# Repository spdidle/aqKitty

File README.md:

# aqkitty

The aqKitty is a kitty shaped PCB that detects air quality, humidity, and temperature, then displays current condition on an OLED screen. Also, its a kitty :3

I made this project to solidify my understanding in KiCad, and my general electronics understanding! I felt that after the blinky board, I wanted to learn much more and do more with KiCad, so I decided to follow the Hermes tutorial on Stasis (although no, I didn't submit to Stasis).

I made this project primarily using KiCad, and used EasyEDA for symbols & footprints of the temp and AQ sensors!

This time around, building this PCB was definitely a step up from the blinky board, because it required more understanding of power nets, decoupling capacitors, pullup resistors, net labels, and efficient PCB layout strategies. I struggled the first time building this because I thought I could just add a sensor and microcontroller and call it a day. I then learned lots of things about slightly more complicated PCBs, requiring more than one capacitor, resistor, and other things.

Overall I had lots of fun making this project and I think it turned out super cute! I will definitely consider building it once I get a heat gun for the sensors >:)

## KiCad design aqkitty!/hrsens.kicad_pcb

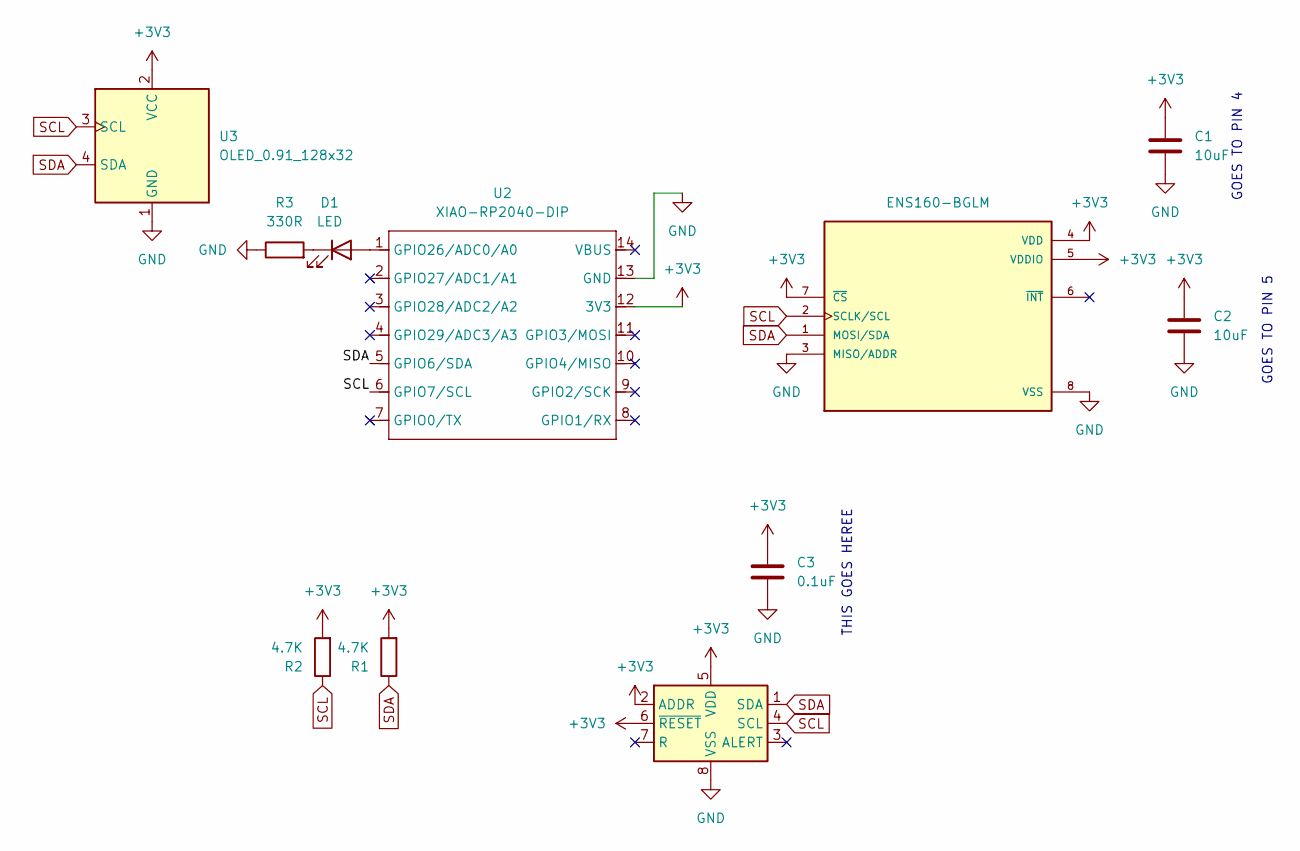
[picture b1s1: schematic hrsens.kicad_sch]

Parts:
C1, C2: 10uF; C_0603_1608Metric_Pad1.08x0.95mm_HandSolder
C3: 0.1uF; C_0603_1608Metric_Pad1.08x0.95mm_HandSolder
D1: LED; LED_0603_1608Metric_Pad1.05x0.95mm_HandSolder
R1, R2: 4.7K; R_Axial_DIN0207_L6.3mm_D2.5mm_P10.16mm_Horizontal
R3: 330R; R_0603_1608Metric_Pad0.98x0.95mm_HandSolder
U1: ENS160-BGLM; XDCR_ENS160-BGLM; PARTREV 1.3
U2: XIAO-RP2040-DIP
U3: OLED_0.91_128x32
U4: SHT30-DIS; Sensirion_DFN-8-1EP_2.5x2.5mm_P0.5mm_EP1.1x1.7mm

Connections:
+3V3: C1.1, C2.1, C3.1, R1.2, R2.2, U1.4 (VDD), U1.5 (VDDIO), U1.7 (~CS), U2.12 (3V3), U3.2 (VCC), U4.2 (ADDR), U4.5 (VDD), U4.6 (~RESET)
GND: C1.2, C2.2, C3.2, R3.1, U1.3 (MISO/ADDR), U1.8 (VSS), U1.9 (VSS), U2.13 (GND), U3.1 (GND), U4.8 (VSS), U4.9 (VSS)
unnamed: D1.2 (A), U2.1 (GPIO26/ADC0/A0)
unnamed: D1.1 (K), R3.2
SCL: R2.1, U1.2 (SCLK/SCL), U2.6 (GPIO7/SCL), U3.3 (SCL), U4.4 (SCL)
SDA: R1.1, U1.1 (MOSI/SDA), U2.5 (GPIO6/SDA), U3.4 (SDA), U4.1 (SDA)

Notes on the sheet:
GOES TO PIN 4
THIS GOES HEREE
GOES TO PIN 5

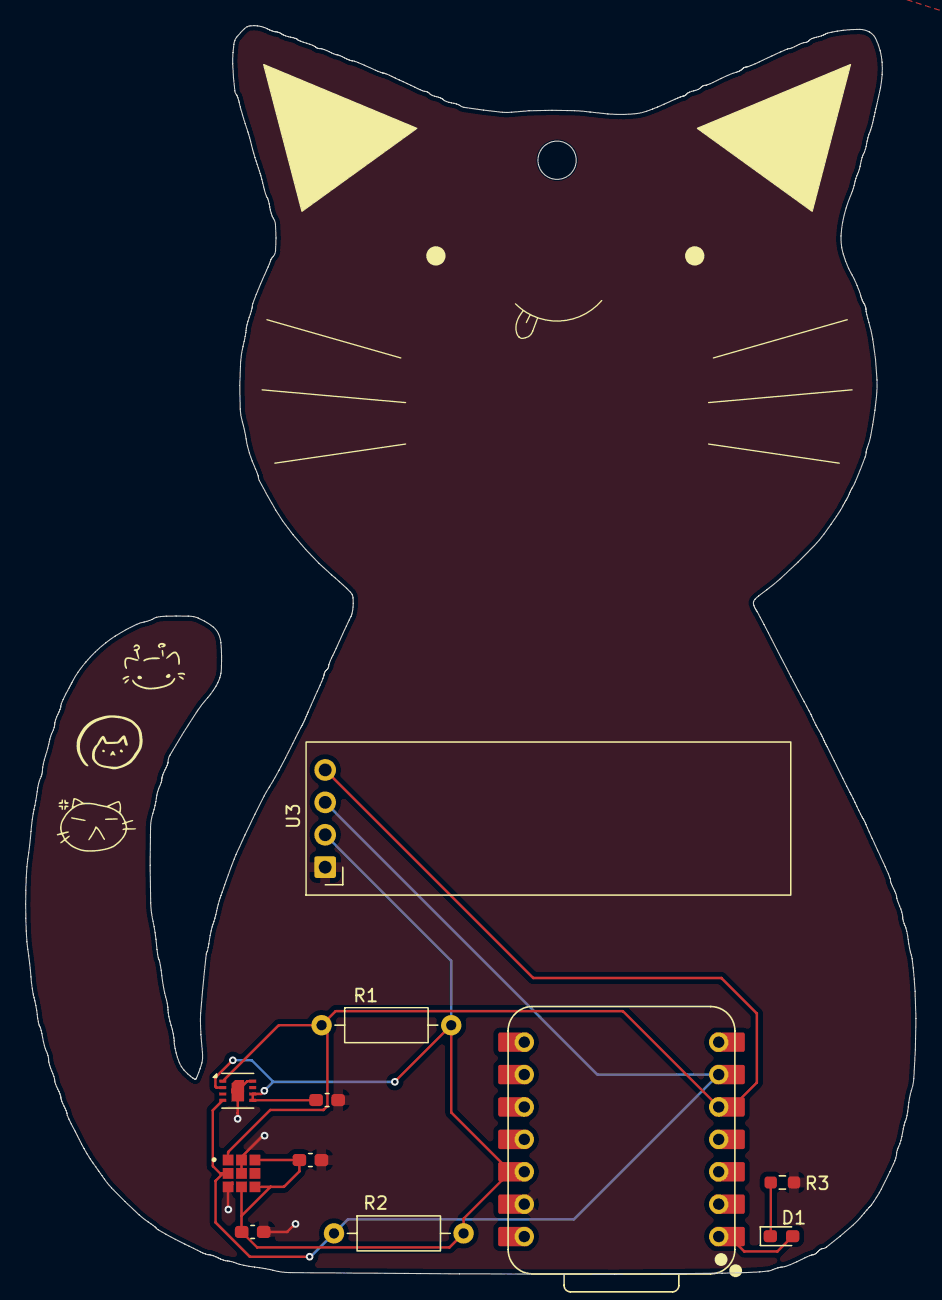
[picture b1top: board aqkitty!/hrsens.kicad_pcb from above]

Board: 2 copper layers, 69.8 x 97.9 mm, 11 parts (0 on the bottom side), 6 nets.

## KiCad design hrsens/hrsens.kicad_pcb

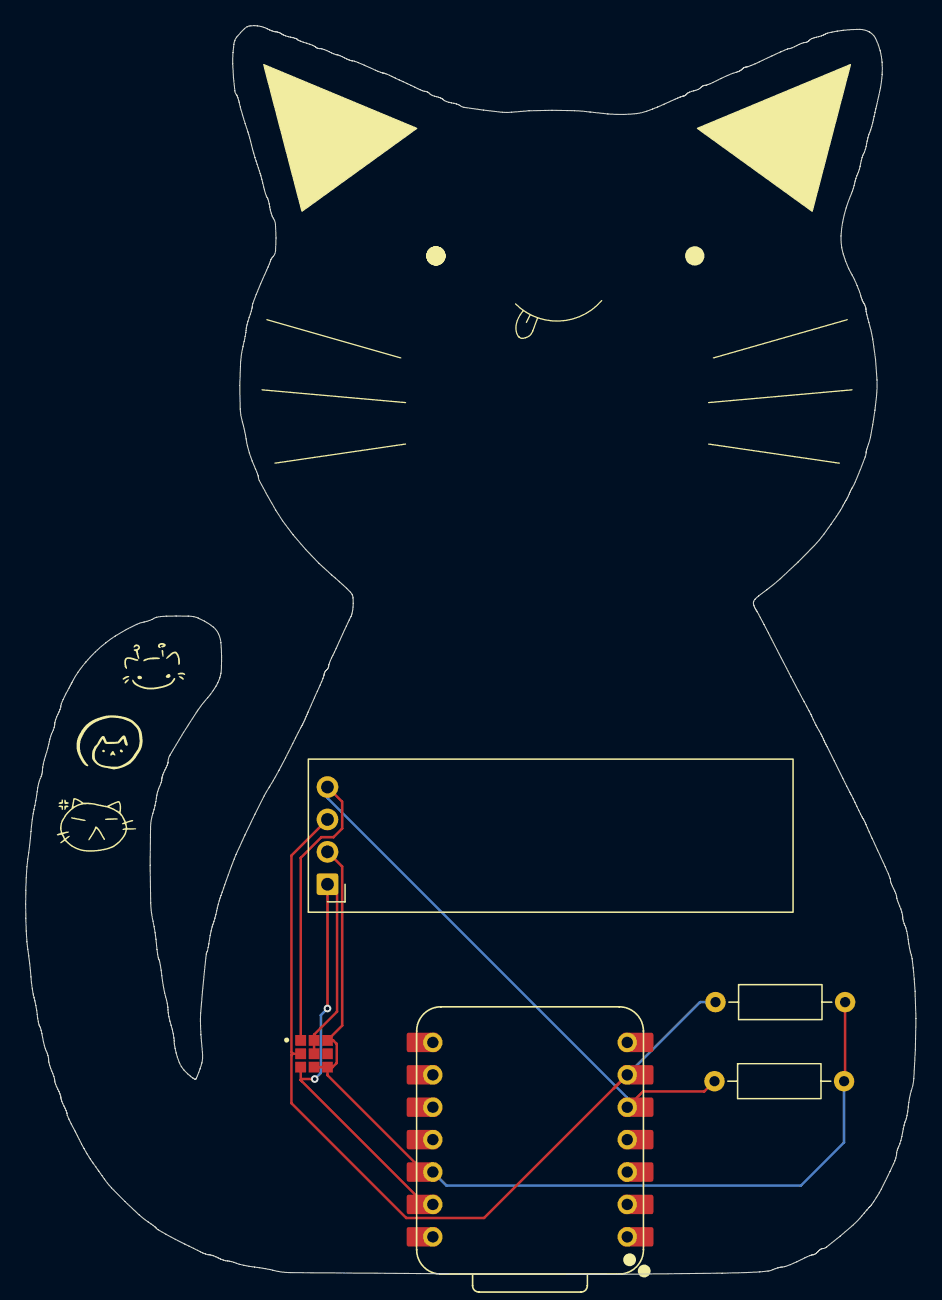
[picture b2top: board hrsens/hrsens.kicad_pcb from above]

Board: 2 copper layers, 69.8 x 97.9 mm, 5 parts (0 on the bottom side), 4 nets.

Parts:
R1, R2: 4.7K; R_Axial_DIN0207_L6.3mm_D2.5mm_P10.16mm_Horizontal
U1: ENS160-BGLM; XDCR_ENS160-BGLM
U2: XIAO-RP2040-DIP
U3: OLED_0.91_128x32

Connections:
/3V3: R1.2, R2.2, U1.4 (VDD), U1.5 (VDDIO), U1.7 (~CS), U2.12 (3V3), U3.2 (VCC)
/SCL: R2.1, U1.2 (SCLK/SCL), U2.6 (GPIO7/SCL), U3.3 (SCL)
/SDA: R1.1, U1.1 (MOSI/SDA), U2.5 (GPIO6/SDA), U3.4 (SDA)
VSS: U1.3 (MISO/ADDR), U1.8 (VSS), U1.9 (VSS), U2.13 (GND), U3.1 (GND)

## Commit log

2026-04-07 ok bye guys! pcb out
    - silkscreened some stuffs
    - touched up some traces again
    tapping out for tonight bluds. i forgot about my homework that was definitely due tomorrow so
2026-04-19 final touches?
    added a mounting hole because why not, i think im done
2026-04-19 fix.. and layout...
    added pullups, temp sensor, then started the NIGHTMARE that is pcb layout
2026-04-24 yay finished pcb layout
    for REAL this time after adding temp sens and also um yes gonna do readme now
2026-04-24 done readme! lets go submit
    hehe 😛
2026-04-24 add schematic photo
    ooops sorry sana
